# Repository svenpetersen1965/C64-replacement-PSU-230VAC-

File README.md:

# C64-replacement-PSU-230VAC-
This is a replacement PSU for the Commodore C64. The original PSUs from the 1980s and early 1990s tend to die and damage the connected C64, so it is recommended to get a new power supply for the C64.
This design is straight forward: a transformer, bridge rectifier and DC/DC converter for the 5VDC and a separat winding for the 9VAC. Nothing fancy. It was paid attention to use parts which are easily available (in Germany). Everything, except the 4 conductor cable for the output voltage are sourced from reichelt.de.
A further goal was a decent documentation.

Find some info on the required cable making <a href="http://tech.guitarsite.de/cable_making.html">on my website</a>

# three-way mains connector
The R/C combination (1MOhm/10nF) between GND and PE has a very positive effect: The capacitive mains couplings that usually happens in cheap SMPS, that are used for the S-Video/HDMI converters, the Pi1541 etc. is suppressed this way. No more flickering when touching the user port or cassette port. Thus, it is recommended to place those components and use a three-way appliance connector for mains.

# Calculation of the BOM prices
The BOM v2.0 was calculated. The total price of the components (case included) is 47.58€ (June 9th, 2020).

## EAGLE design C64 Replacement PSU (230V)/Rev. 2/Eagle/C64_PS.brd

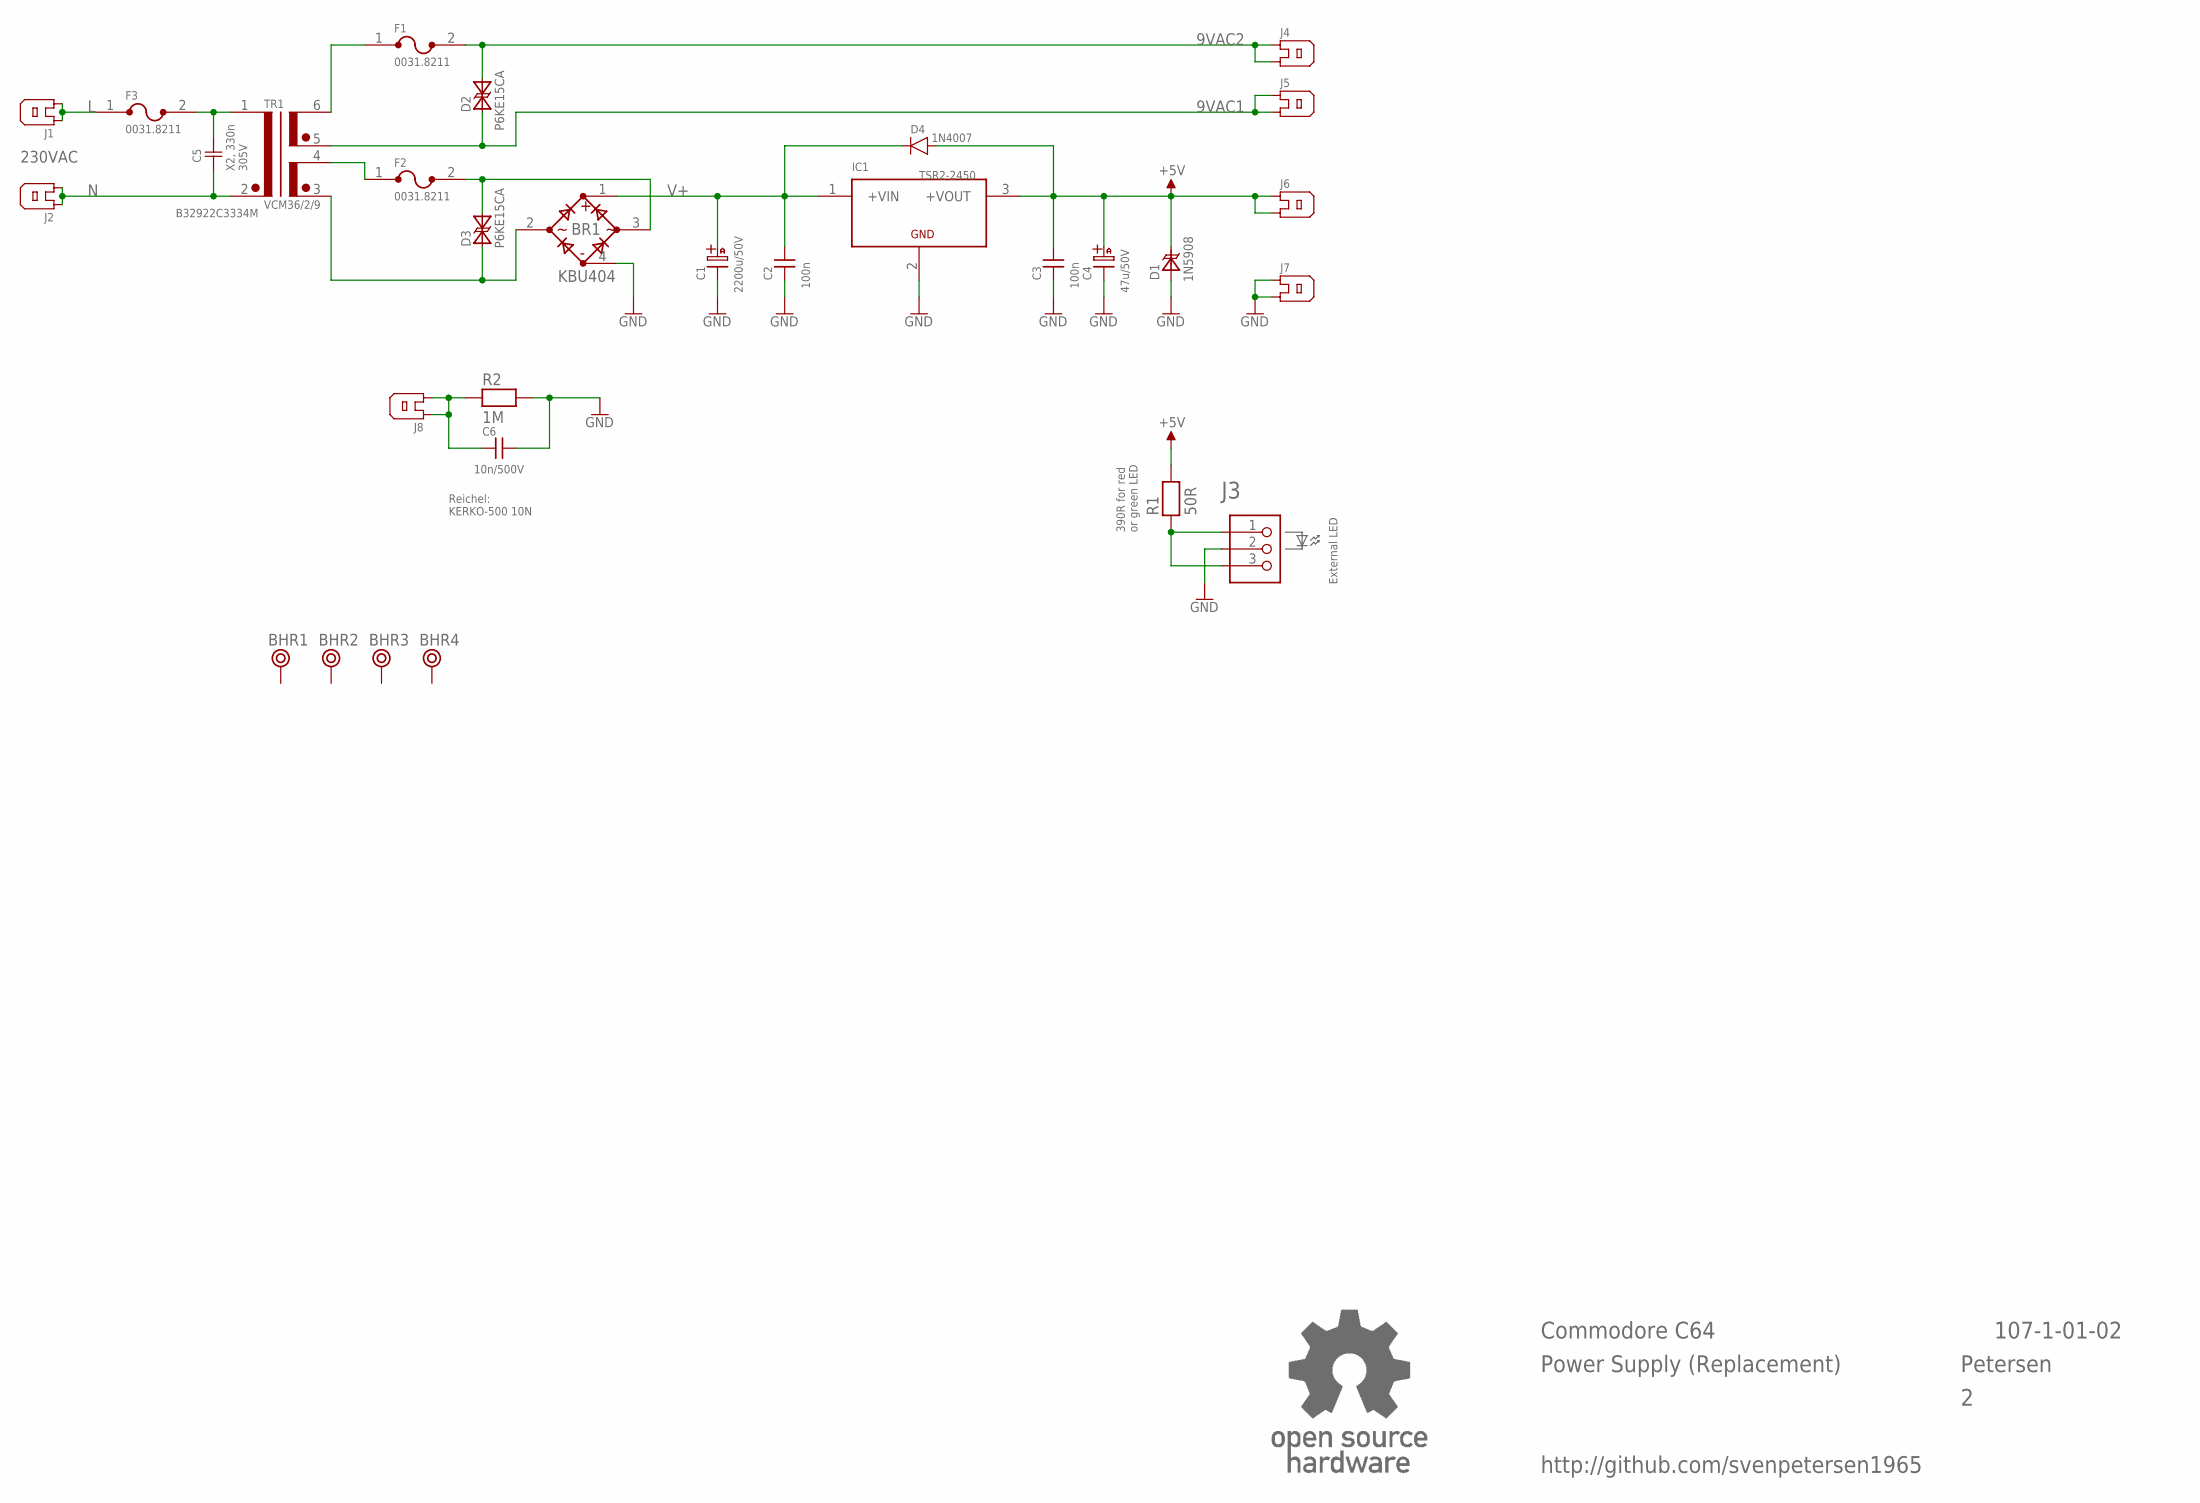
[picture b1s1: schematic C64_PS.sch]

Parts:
BHR1, BHR2, BHR3, BHR4: BOHR3,3
BR1: KBU404; KBU
C1: 2200u/50V; C18/7,5
C2, C3: 100n; C-5
C4: 47u/50V; C07/2,5
C5: B32922C3334M; C-18X8-RM15
C6: 10n/500V; C-5
D1: 1N5908; CB429
D2, D3: P6KE15CA; CB417
D4: 1N4007; DO-41
F1, F2, F3: 0031.8211
IC1: TSR2-2450; TSR2
J1, J2, J4, J5, J6, J7, J8: FLA6,3
J3: PINHD-1X3; 1X03
R1: 50R; R-10
R2: 1M; R-10
TR1: VCM36/2/9; VCM36_2_9
U$17: OPEN_SOURCE_HW; OPENHW

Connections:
9VAC1: D2.A (A1), J5.1, J5.2, TR1.5 (SEC12)
9VAC2: D2.K (A2), F1.2, J4.1, J4.2
+5V: C3.2, C4.A (+), D1.K, D4.A, IC1.3 (+VOUT), J6.1, J6.2, R1.2
GND: BR1.4 (-), C1.-, C2.1, C3.1, C4.K (-), C6.2, D1.A, IC1.2 (GND), J3.2, J7.1, J7.2, R2.2
L: F3.1, J1.1, J1.2
N: C5.1, J2.1, J2.2, TR1.2 (PRI2)
unnamed: F1.1, TR1.6 (SEC11)
unnamed: J3.1, J3.3, R1.1
unnamed: F2.1, TR1.4 (SEC21)
unnamed: BR1.2 (AC1), D3.A (A1), TR1.3 (SEC22)
unnamed: BR1.3 (AC2), D3.K (A2), F2.2
unnamed: C5.2, F3.2, TR1.1 (PRI1)
PE: C6.1, J8.1, J8.2, R2.1
V+: BR1.1 (+), C1.+, C2.2, D4.K, IC1.1 (+VIN)

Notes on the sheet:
230VAC
External LED
X2, 330n 305V
Commodore C64
Power Supply (Replacement)
107-1-01-02
Petersen
390R for red or green LED
Reichel: KERKO-500 10N
http://github.com/svenpetersen1965

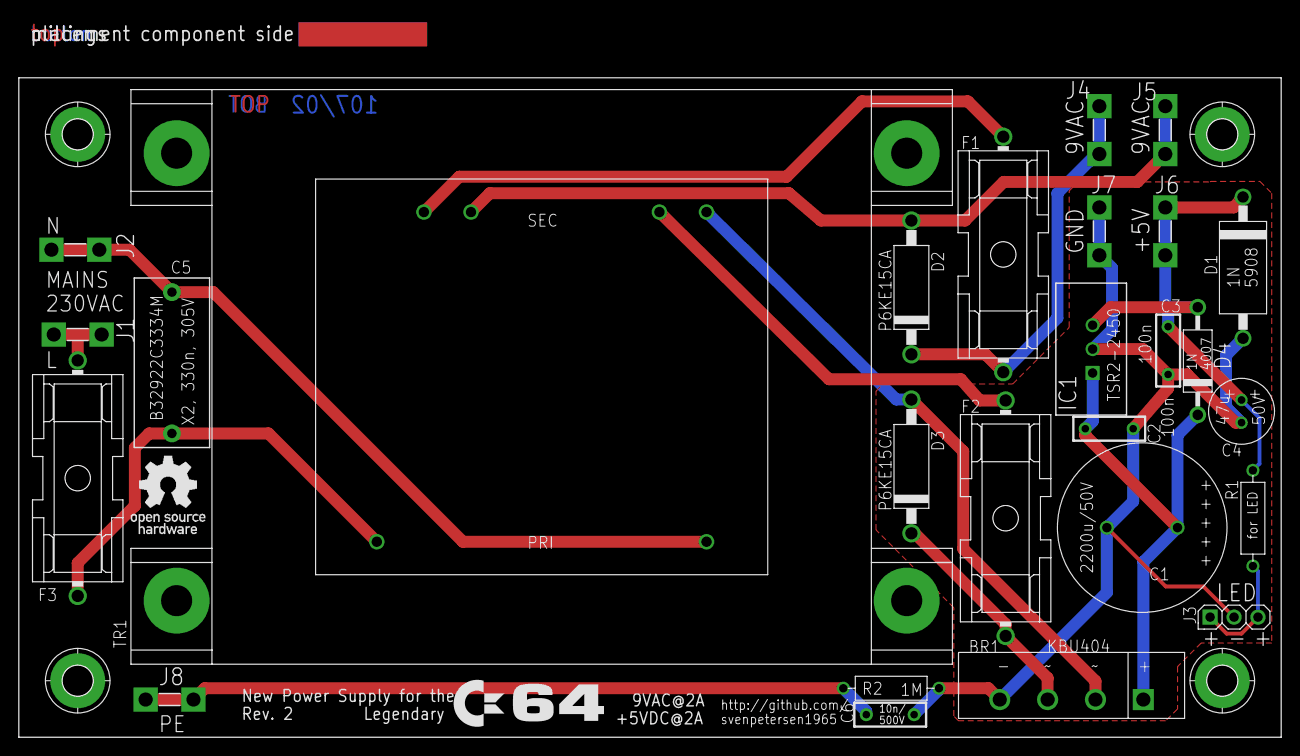
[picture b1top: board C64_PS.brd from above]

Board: 2 copper layers, 133.9 x 76.2 mm, 34 parts (0 on the bottom side), 14 nets.

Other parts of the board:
U$13: PCB-TITLE/
U$14: 2LAYER
U$15: C64_LOGO

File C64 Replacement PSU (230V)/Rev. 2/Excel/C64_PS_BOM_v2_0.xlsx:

C64 Power Supply (Replacement) Rev. 2
Bill of Material Rev. 2.0
Pos. | Each | Value | Footprint | Ref.-No. | Comment
1 | 1 | 107-2-01-02 | 2 layer | PCB Rev. 2 | 2 layer, Cu 35µ, HASL, 134mm x 70mm, 1.6mm FR4
2 | 6 | 6,3 x 0,8 | FLA6,3 | J1, J2, J4, J5, J6, J7 | Spade connector f. PCB, Reichelt RND 465-00018 (100ea)
3 | 1 | 6,3 x 0,8 | FLA6,3 | J8 | not assembled
4 | 1 | 1x03 | 1X03 | J3 | Pin header, Reichelt RND 205-00624
5 | 3 | 0031.8201 | 0031.8201 | (F1), (F2), (F3) | Fuse holder, Schurter 0031.8201, Reichelt PL OGN-22,5
6 | 1 | 2A/T | 5x20mm | F1 | glass fuse 5x 20, 2A t
7 | 2 | 2A/T | 5x20mm | F2 | glass fuse 5x 20, 2A t
8 | 3 | 0,16A/T | 5x20mm | F3 | glass fuse 5x 20, 0,16A t
9 | 2 | 100n | C-5 | C2, C3 | 100nF, 50V, RM5
10 | 1 | 2200u/50V | C18/7,5 | C1 | Elko Æ18mm/RM 7,5, 105°C, Reichelt RAD FC 2.200/50
11 | 1 | 47u/50V | C07/2,5 | C4 | Elko Æ7mm/RM 2,5, 105°C, Reichelt NHG-A 47U 50
12 | 1 | 49.9R | R-10 | R1 | 49.9W, 1/4W
13 | 1 | B32922C3334 | C-18x8-RM15 | C5 | X2-capacitor, EPCOS, 330 nF, 305 V, RM 15,0, Reichelt B32922C3334
14 | 1 | KBU404 | KBU | BR1 | HY, bridge rectifier, 4A, Reichelt KBU4G
15 | 2 | P6KE15CA | CB417 | D2, D3 | Littlefuse, Reichelt P6KE 15CA
16 | 1 | 1N5908 | CB429 | D1 | ST Micro, Reichelt 1N 5908
17 | 1 | TSR 2-2450 | TSR 2 | IC1 | 2A: Traco, Reichelt TSR 2-2450. (alternative 1.5A: DC/DC-converter RECOM, Reich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
18 | 1 | VCM36/2/9 | VCM36_2_9 | TR1 | Block VCM36/2/9, Trafo 230V/2x9V, 2A, Reichelt EI 66/23 209
19 | 2m | 4x0,75qmm | cable |  | www.wamo-shop.de, Art.-Nr. V-198-003 or similar
20 | 1 | RND 455-00220 | enclosure |  | RND, Reichelt RND 455-00220
21 | 4 | M3 x 6mm | screw
22 | 6 | 6,3 x 0,8 mm, rot, ISO | spade terminal |  | Reichelt RND 465-00067
23 | 1 | MAS 70S | DIN connector 7p |  | Reichelt MAS 70S
24 | 1 | Strain-reliefe 5,0-6,8mm | Strain-relieve |  | Reichelt KAZU 1
25 | 1 | mains cable 2p. Euro-double connector
26 | 1 | Einbaustecker C8 |  |  | Mains power cable panel connector, European Design C8, Reichelt B-AC-E
27 | 1 | L-53MBD BLUE | 5mm LED, blau |  | Kingbright 5mm LED, Reichelt SLK 5MM BL
28 | 1 | RTC-51 | RTC-51 |  | Mounting clip for LED 5 mm, Reichelt MONTAGERING 5MM
29 | 1 | Dupont Crimp housing 3p |  |  | for LED
30 | 2 | Dupont Crimp contacts, female |  |  | for LED
31 | 20cm | wire, 0.25mm² red
32 | 20cm | wire, 0.25mm² black
33 | 2cm | shrinkable sleeve |  |  | for LED
34 | 20cm | wire, 0.75mm², blue |  |  | for C8 mains connector
35 | 20cm | wire 0.75 mm², black |  |  | for C8 mains connector
36 | 3cm | shrinkable sleeve |  |  | for C8 mains connector
37 | 2 | screw M3x16, flathead |  |  | for C8 mains connector
38 | 6 | Nuit M3, self locking |  |  | for C8 mains connector and transformer
39 | 6 | Washer 3,2 |  |  | for C8 mains connector and transformer
40 | 2 | screw M3x8 |  |  | for transformer
41 | 1 | 1N4007 | DO-41 | D4
42 | 1 | 1M | R-10 | R2 | not assembled
43 | 1 | 10n/500V | C-5 | C6 | not assembled, Reichelt KERKO-500 10N

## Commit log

2019-03-15 Initial aupload
2019-03-15 Initial file upload
2019-03-15 Added pictures
2019-03-15 No good, uncomplete information
2019-03-15 Better label
    Includes the required information
2020-06-09 BOM calculation added
    Prices of June 9th, 2020
2020-08-10 Silk Screen Update
2022-02-26 Gerbers removed
